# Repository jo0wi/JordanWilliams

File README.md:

# Jordan Williams – Electrical & FPGA Design Portfolio

 B.S. Electrical Engineering, University of Georgia (2026)  
 Focus Areas: FPGA Design, Digital Hardware, Embedded Systems, PCB Layout  

## About Me
I’m passionate about digital hardware and embedded system design, with experience in Verilog, FPGA development (Basys3/Nexys A7), and PCB design using Altium Designer.  
My projects span from HDL-based CPU simulation to real PCB hardware for satellite subsystems.

## Featured Projects
- **[UART Echoing Transceiver](./HDL_Projects/uart%20transceiver)** - UART Transceiver that displays ascii code from serial terminal and echos it back to the terminal over USB.  
- **[Verilog Single-Cycle CPU](./HDL_Projects/Verilog_SCC)** - ARM-like CPU simulation with custom ISA and compiler for computer architecture course.  
- **[Reaction Timer (FPGA)](./HDL_Projects/Digital_Design_Labs/Final%20Project/)** - Reaction Timer implemented on the Basys3 FPGA Development Board   

## Skills
- **HDL Design:** Verilog, Vivado, Icarus Verilog  
- **Hardware Design:** Altium Designer, Eagle, PCB Testing & Validation  
- **Embedded:** Arduino, Raspberry Pi, Python, C/C++  
- **Analysis:** MATLAB, Simulink, GTKWave

---
**Contact:** www.linkedin.com/in/jordan-williams-029b55268 | Jordan.Williams2@uga.edu

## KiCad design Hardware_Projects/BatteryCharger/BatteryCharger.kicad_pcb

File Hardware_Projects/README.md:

# Hardware Projects — PCB Designs

PCB projects covering schematic capture, layout, BOM generation, and CAM output for fabrication.

---

## Boards

| Project | Tool | Summary |
|---|---|---|
| [Motor Controller](./Motor_Controller/) | KiCad 9.0.5 | Battery-powered DC motor controller built around the ATmega328P with joystick input, onboard USB-C charging, and a USB-UART debug bridge. |

---

## How to Open

Open `.kicad_pro` in KiCad 9.0.5, then use the project manager to navigate the schematic (`.kicad_sch`) and layout (`.kicad_pcb`).

---

## Other Hardware Work

PCB and harness work for the SSRL MOCI 6U CubeSat mission and the UGA Formula SAE EV high-voltage accumulator are not in this folder — those live in private institutional repos. See the experience section in the [root README](../README.md) for context.

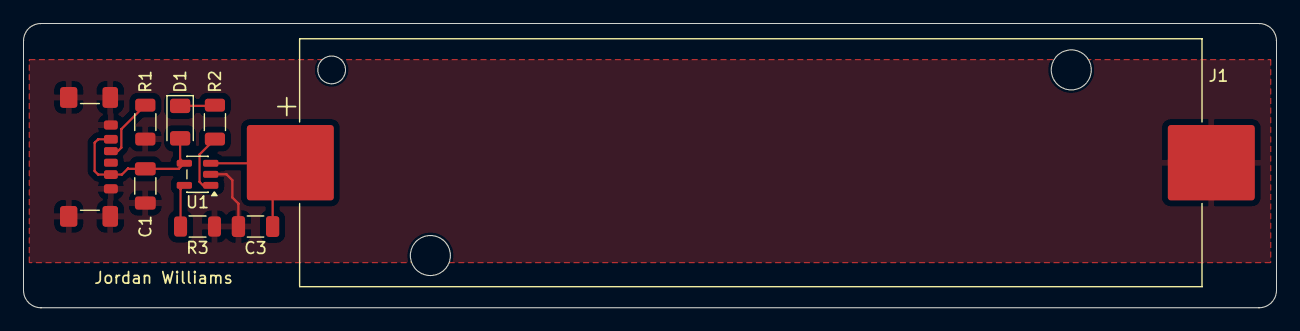
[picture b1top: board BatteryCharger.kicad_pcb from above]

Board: 2 copper layers, 108.0 x 24.5 mm, 9 parts (0 on the bottom side), 7 nets.

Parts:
C1, C3: 4.7uF; C_1206_3216Metric
D1: IR26-21C_L110_TR8; LED_1206_3216Metric
J1: Screw_Terminal_01x02; BatteryHolder_Keystone_1042_1x18650
P1: USB_C_Plug_USB2.0; USB_C_Receptacle_GCT_USB4135-GF-A_6P_TopMnt_Horizontal
R1: 5.1k; R_1206_3216Metric
R2: 470; R_1206_3216Metric
R3: 2k; R_1206_3216Metric
U1: MCP73831-2-OT; SOT-23-5

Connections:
/Batt+: C3.1, J1.1, U1.3 (V_{BAT})
/CC: P1.A5 (CC), R1.1
/PROG: R3.2, U1.5 (PROG)
/PWR_RAIL: C1.1, D1.2 (A), P1.A9 (VBUS), P1.B9 (VBUS), U1.4 (V_{DD})
GND: C1.2, C3.2, J1.2, P1.A12 (GND), P1.B12 (GND), P1.S1 (SHIELD), R1.2, R3.1, U1.2 (V_{SS})
unnamed: D1.1 (K), R2.1
unnamed: R2.2, U1.1 (STAT)

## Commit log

2025-11-10 Create HDL_Projects
2025-11-10 added file structure as well as some projects
2025-11-10 update main readme
2025-11-10 updated readme for digital design final project
2025-11-10 readme
2025-11-14 added cache emulator
2025-12-12 Clkgen.v VGA_Controller.v tb_25MHz_Clk.v
2025-12-24 VGA controller is now working.
2025-12-30 created uart reciever modula (untested)
2025-12-30 add testbench for UART_RX module
2025-12-30 uart_tb
2025-12-30 uart rx working
2025-12-30 add .gitignore file to exclude build artifacts and temporary files
2025-12-31 add UART_TX module implementation with state machine for transmission
2025-12-31 uart rx and tx modules working together in sim
2026-01-06 UART_transceiver wroking on the nexys a7 board and displaying on seven segment display
2026-01-06 update README to include UART Echoing Transceiver project and refine skills section
2026-01-09 Added vga controller to featured
2026-01-09 Fix formatting of FPGA VGA Controller entry in README
2026-01-09 Fix formatting for Reaction Timer project entry
2026-01-09 Enhance Reaction Timer project description
    Updated the description of the Reaction Timer project to include details about the LCD pmod.
2026-01-09 Update contact information format in README
2026-01-09 Update contact section formatting in README
2026-01-09 Fix contact section formatting in README
    Updated contact information formatting in README.
2026-01-09 added uart interface project for esp32 commands
2026-01-10 added air quality sensor project and bluetooth module for m5stick
2026-01-10 added som hardware projects
2026-01-10 formatting
2026-01-10 added documentation to proojects
2026-01-12 readme update
2026-01-23 Update project description for Air Quality Sensor
2026-01-23 Update UART Transceiver project link in README
2026-02-14 Update email address in README
2026-03-06 update repo with new README files
2026-03-11 Update README to remove demo and simulation placeholders
    Removed demo and simulation sections from README.
2026-03-11 Add initial implementation for magnetic levitator control system
    - Created blank file in milestone 2 for future use.
    - Implemented basic ADC reading from Hall sensor in levitator.py.
    - Added controller logic in milestone 3 with discrete controller coefficients in controller.py.
    - Developed MOSFET testing script in mosfettest.py to sweep PWM duty cycle.
    - Implemented a simple proportional control algorithm in simple.py for levitation.
    - Created test script in test.py to validate PWM control and Hall sensor readings.
2026-03-11 Add README and configuration files for magnetic levitation project
2026-03-11 Refine README: Update demo video label and remove simulation section
2026-03-11 Update README to include demo GIF of levitation and replace video file
2026-03-11 Add initial files and implement basic control for magnetic levitator
    - Created blank file for milestone 2.
    - Implemented hall sensor reading in `levitator.py` for ADC value and voltage output.
    - Added new file `P.py` for milestone 4.
    - Developed `controller.py` for milestone 3 with a discrete controller for levitation.
    - Created `mosfettest.py` to test MOSFET PWM control.
    - Implemented `simple.py` for a basic proportional control approach to levitation.
2026-03-11 Add final report for magnetic levitation project detailing system modeling, control, and implementation
2026-03-11 updated structure
2026-03-11 updated profile readme
2026-03-16 Refactor code structure for improved readability and maintainability
2026-03-16 Refactor code structure and remove redundant sections for improved readability and maintainability
2026-03-16 Update synthesis and implementation reports for UART transceiver project
    - Updated report timestamps in DRC, routing, IO placement, methodology, power, and timing summary reports to reflect new synthesis run on March 16, 2026.
    - Modified TCL script for synthesis to remove unnecessary parameters.
    - Adjusted XML configuration for synthesis and implementation runs.
    - Enhanced xsimSettings.ini for better scope name visibility.
    - Added new jobs configuration XML for tracking synthesis and implementation runs.
    - Updated binary files related to synthesis and implementation processes.
2026-03-16 Update demo GIF reference in README.md and add new demo GIF file
2026-03-16 readme edit
2026-03-16 Remove demo section from README
    Removed demo section and placeholder from README.
2026-03-18 Update power supply requirement from 9V to 32V
2026-05-06 Add new files for ball beam control system simulation cache
    - Added video file simscapevid.mp4 for visual representation of the system.
    - Created checksumOfCache.mat to store cache checksum for closed-loop simulation.
    - Introduced simulink_cache.xml to manage Simulink cache attributes.
    - Added varInfo.mat to hold variable information for the closed-loop model.
2026-05-06 added *.mp4 to .gitignore
2026-05-06 Re-add *.mp4 to .gitignore
2026-05-09 Add initial files for Battery Charger project and README documentation
    - Created lock files for Battery Charger schematic and PCB to manage autosave.
    - Added README.md to provide an overview of hardware projects, including project summaries and instructions for opening Altium projects.
2026-05-09 Enhance documentation for Air Quality Sensor Project and Cache Emulator
    - Added detailed architecture diagram and project structure for the Air Quality Sensor Project.
    - Expanded specifications and operational details for the Air Quality Sensor Project.
    - Improved instructions on setting up and running the Air Quality Sensor Project.
    - Updated README for Cache Emulator with a comprehensive project description and structure.
    - Clarified build and run instructions for the Cache Emulator.
    - Added implementation notes and output details for the Cache Emulator.
2026-05-18 Save current changes
2026-05-18 Save current changes and remove duplicate case-mismatched entries
2026-05-18 chore: update code structure for better readability and maintainability
2026-05-18 chore: remove obsolete README files and delete Motor Controller subproject
2026-05-18 added motor controller project, bom, and readme
2026-05-18 Fix image paths in Motor Controller README
    Updated image paths in README for Motor Controller.
2026-05-18 Fix front image path in README.md
    Updated image path for the front board image.
2026-05-18 Fix front image path in README.md
    Updated image paths for the front board image in README.
2026-05-18 Fix image paths in Motor_Controller README
    Updated image paths in README for consistency.
2026-05-18 Refactor README and remove lock files
    - Updated README.md to reflect the transition from Altium to KiCad, including project details and tool versions.
    - Deleted lock files for BatteryCharger schematic and PCB to clean up the repository.
